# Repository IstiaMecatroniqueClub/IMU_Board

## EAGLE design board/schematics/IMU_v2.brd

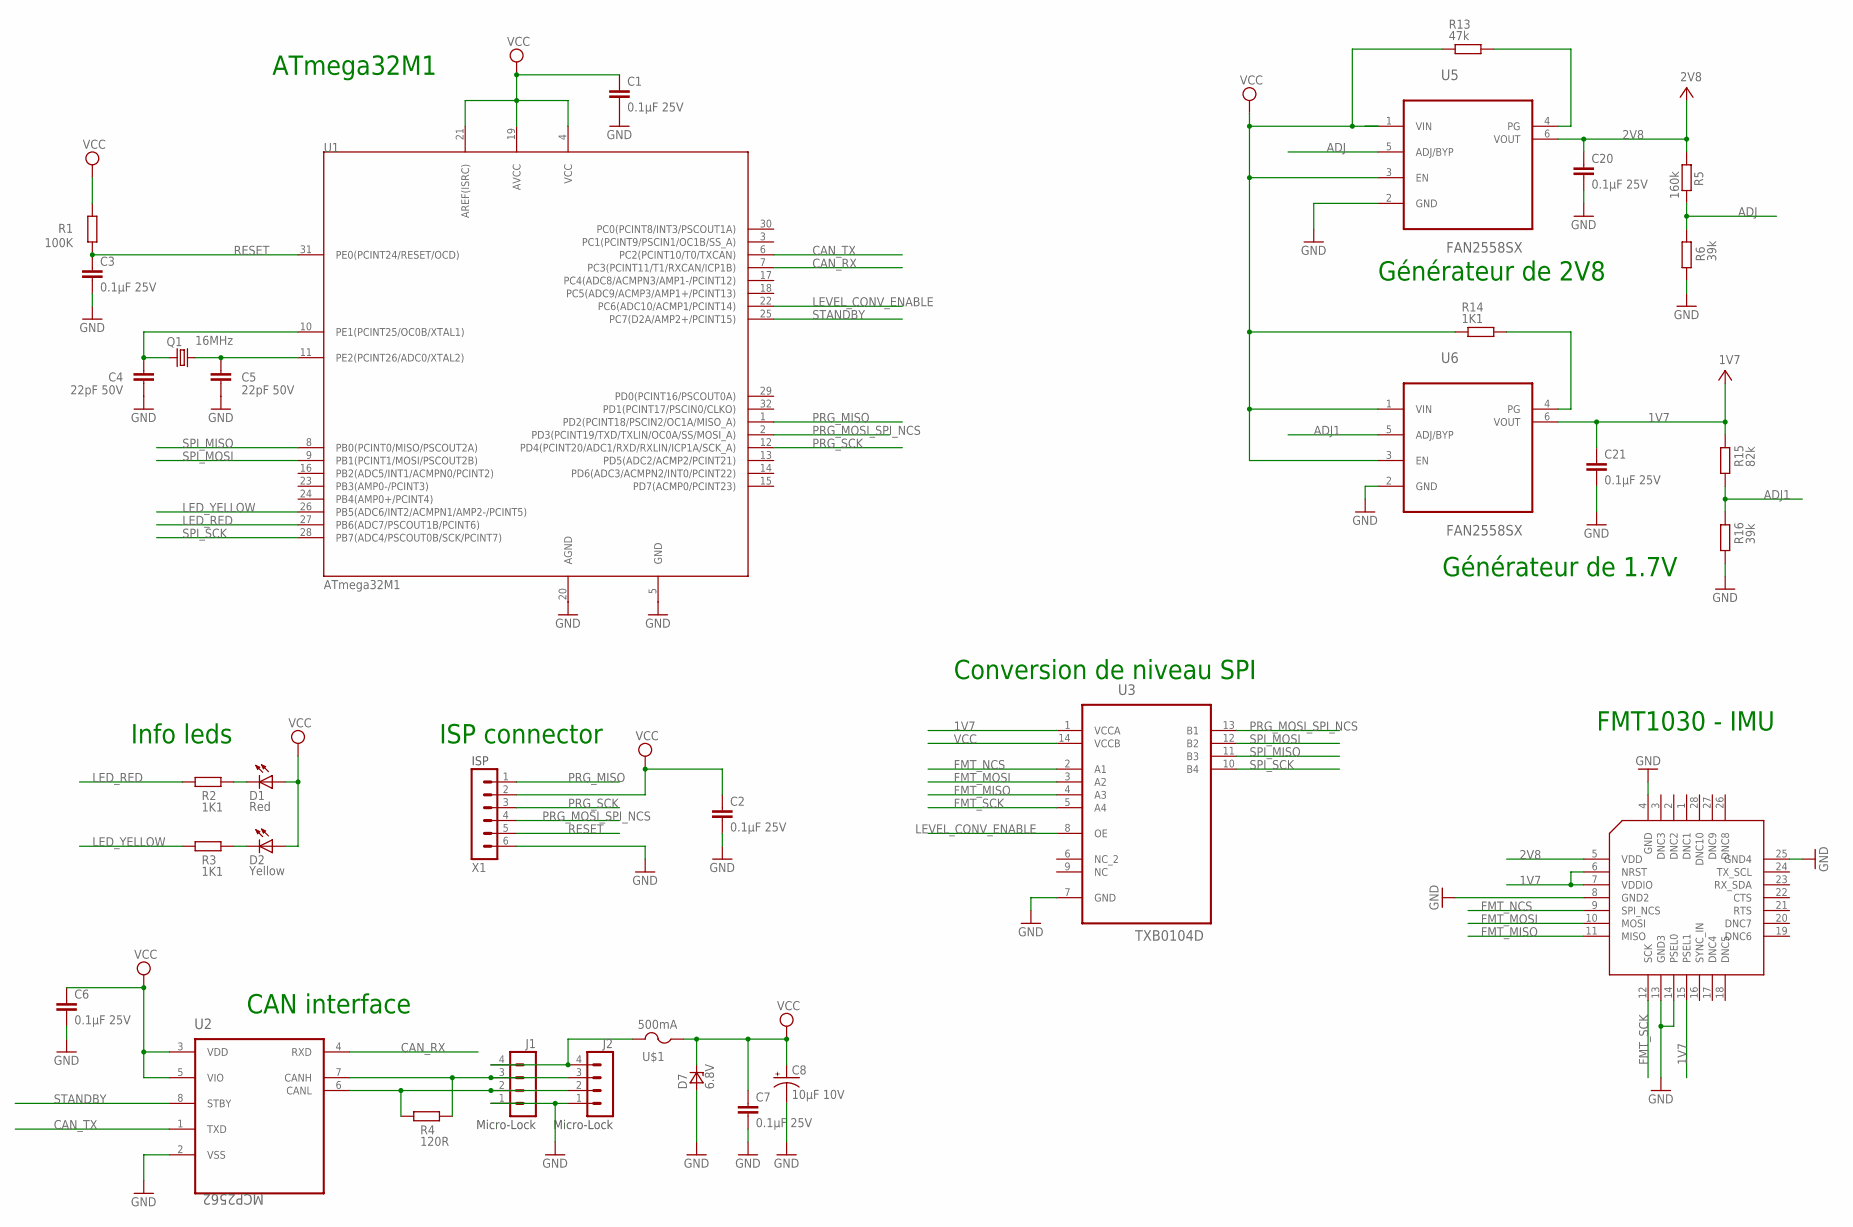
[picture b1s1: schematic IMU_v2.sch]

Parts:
C1, C2, C3, C6, C7, C20, C21: 0.1µF 25V; C2012
C4, C5: 22pF 50V; C2012
C8: 10µF 10V; EIA3216
D1: Red; VLD
D2: Yellow; VLD
D7: 6.8V; DO-214AA
J1, J2: Micro-Lock; 504195-0470
Q1: 16MHz; SMD_KX7
R1: 100K; R2012
R2, R3, R14: 1K1; R2012
R4: 120R; R2012
R5: 160k; R2012
R6, R16: 39k; R2012
R13: 47k; R2012
R15: 82k; R2012
U1: ATmega32M1; TQFP32
U2: MCP2562; SOIC8
U3: TXB0104D; SOIC127P600X175-14N
U5, U6: FAN2558SX; SOT95P270X145-6N
U$1: 500mA; EIARS-481-2
U$2: FMT1030; S28
X1: ISP; MINITEK_127_6WAY_SMD

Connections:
1V7: C21.1, R15.1, U3.1 (VCCA), U6.6 (VOUT), U$2.6 (NRST), U$2.7 (VDDIO), U$2.15 (PSEL1)
2V8: C20.1, R5.1, U5.6 (VOUT), U$2.5 (VDD)
ADJ: R5.2, R6.1, U5.5 (ADJ/BYP)
ADJ1: R15.2, R16.1, U6.5 (ADJ/BYP)
CAN_RX: U1.7 (PC3(PCINT11/T1/RXCAN/ICP1B)), U2.4 (RXD)
CAN_TX: U1.6 (PC2(PCINT10/T0/TXCAN)), U2.1 (TXD)
FMT_MISO: U3.4 (A3), U$2.11 (MISO)
FMT_MOSI: U3.3 (A2), U$2.10 (MOSI)
FMT_NCS: U3.2 (A1), U$2.9 (SPI_NCS)
FMT_SCK: U3.5 (A4), U$2.12 (SCK)
GND: C1.2, C2.2, C3.2, C4.2, C5.2, C6.2, C7.2, C8.C (-), C20.2, C21.2, D7.A, J1.1, J2.1, R6.2, R16.2, U1.5 (GND), U1.20 (AGND), U2.2 (VSS), U3.7 (GND), U5.2 (GND), U6.2 (GND), U$2.4 (GND), U$2.8 (GND2), U$2.13 (GND3), U$2.14 (PSEL0), U$2.25 (GND4), X1.6
LED_RED: R2.2, U1.27 (PB6(ADC7/PSCOUT1B/PCINT6))
LED_YELLOW: R3.2, U1.26 (PB5(ADC6/INT2/ACMPN1/AMP2-/PCINT5))
LEVEL_CONV_ENABLE: U1.22 (PC6(ADC10/ACMP1/PCINT14)), U3.8 (OE)
unnamed: D1.C, R2.1
unnamed: D2.C, R3.1
unnamed: J1.4, J2.4, U$1.2
unnamed: J1.2, J2.2, R4.2, U2.6 (CANL)
unnamed: J1.3, J2.3, R4.1, U2.7 (CANH)
unnamed: C5.1, Q1.3 (2), U1.11 (PE2(PCINT26/ADC0/XTAL2))
unnamed: C4.1, Q1.1, U1.10 (PE1(PCINT25/OC0B/XTAL1))
unnamed: R13.1, U5.4 (PG)
unnamed: R14.2, U6.4 (PG)
PRG_MISO: U1.1 (PD2(PCINT18/PSCIN2/OC1A/MISO_A)), X1.1
PRG_MOSI_SPI_NCS: U1.2 (PD3(PCINT19/TXD/TXLIN/OC0A/SS/MOSI_A)), U3.13 (B1), X1.4
PRG_SCK: U1.12 (PD4(PCINT20/ADC1/RXD/RXLIN/ICP1A/SCK_A)), X1.3
RESET: C3.1, R1.1, U1.31 (PE0(PCINT24/RESET/OCD)), X1.5
SPI_MISO: U1.8 (PB0(PCINT0/MISO/PSCOUT2A)), U3.11 (B3)
SPI_MOSI: U1.9 (PB1(PCINT1/MOSI/PSCOUT2B)), U3.12 (B2)
SPI_SCK: U1.28 (PB7(ADC4/PSCOUT0B/SCK/PCINT7)), U3.10 (B4)
STANDBY: U1.25 (PC7(D2A/AMP2+/PCINT15)), U2.8 (STBY)
VCC: C1.1, C2.1, C6.1, C7.1, C8.A (+), D1.A, D2.A, D7.C, R1.2, R13.2, R14.1, U1.4 (VCC), U1.19 (AVCC), U1.21 (AREF(ISRC)), U2.3 (VDD), U2.5 (VIO), U3.14 (VCCB), U5.1 (VIN), U5.3 (EN), U6.1 (VIN), U6.3 (EN), U$1.1, X1.2

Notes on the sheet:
ISP connector
CAN interface
ATmega32M1
Générateur de 2V8
Générateur de 1.7V
Info leds
Conversion de niveau SPI
FMT1030 - IMU

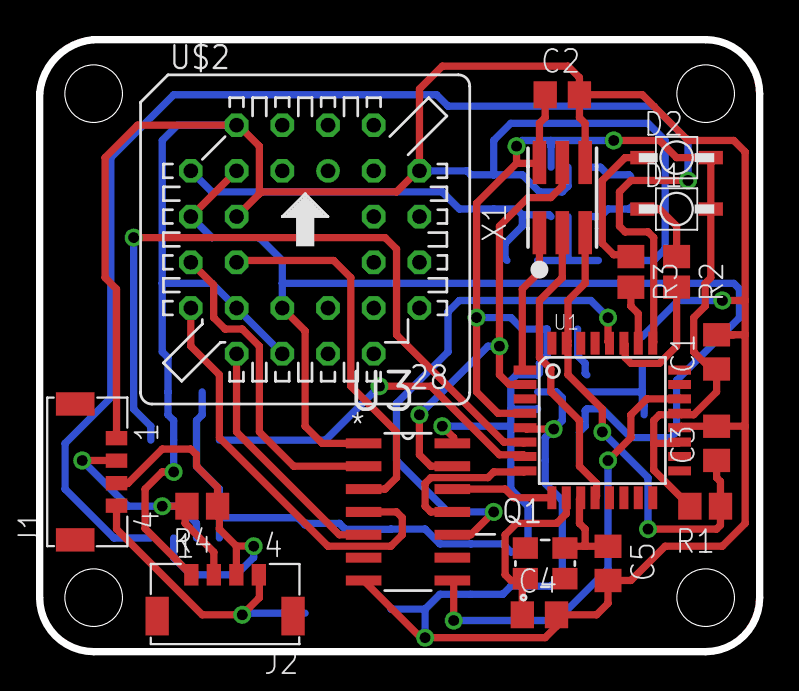
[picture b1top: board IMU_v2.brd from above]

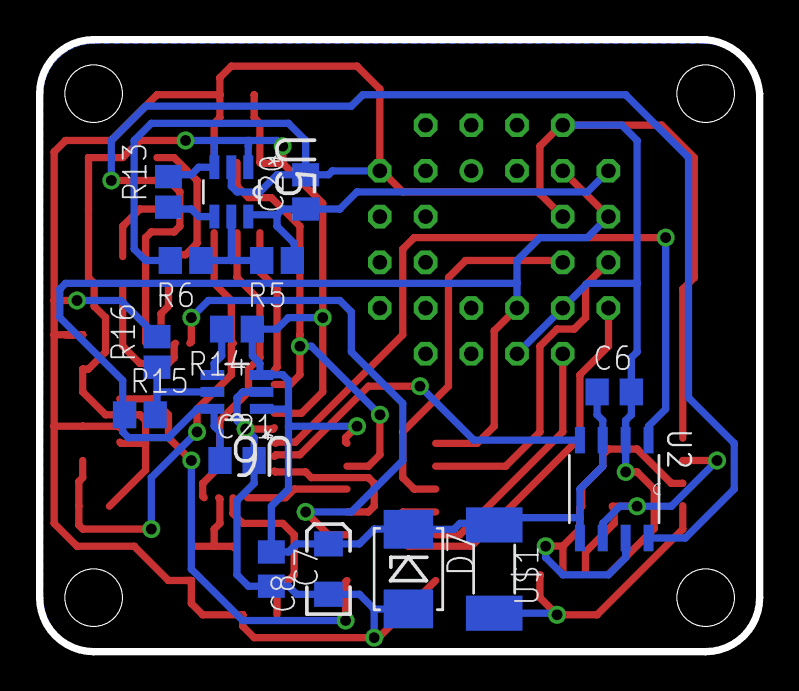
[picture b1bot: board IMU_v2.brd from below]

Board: 2 copper layers, 40.0 x 34.0 mm, 34 parts (16 on the bottom side), 32 nets.

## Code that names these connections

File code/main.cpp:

//! \file main.cpp
//! \brief Main file
//! \author Franck Mercier, Remy Guyonneau
//! \date 2017 05 11
//!
//! Main file for the IMU

#include <util/delay.h>
#include <avr/io.h>
#include <avr/interrupt.h>
#include <string.h> // memcpy


#include "led.h"
#include "spi.h"
#include "fmt1030.h"


// Configuration declaration for the RED LED wiring
#define LED_RED_PORT PORTB //!< The ATMega port where the red LED is wired
#define LED_RED_PIN  6     //!< The ATMega pin where the red LED is wired 
#define LED_RED_POL  0     //!< The polarity of the red LED 

// Configuration declaration for the YELLOW LED wiring
#define LED_YELLOW_PORT PORTB //!< The ATMega port where the red LED is wired
#define LED_YELLOW_PIN  5     //!< The ATMega pin where the red LED is wired 
#define LED_YELLOW_POL  0     //!< The polarity of the red LED 



#define DATA_ID     0X90
#define INPUT_ID    0X77

//! \fn void initCANBus()
//! \brief Intialize the CAN Bus.
//!
//! Function that initializes the CANBus according to the wiring and the needed speed (500kb/s).
//! It also enable the CAN module interruptions
void initCANBus(){
    // Enable of CAN transmit
    DDRC|=0x80; // Configuration of the standby pin as an output
                // (for a transceiver MCP2562 with the stby pin wired to the uC PC7)
    // Enable the MCP2562 (STANDBY to 0)
    PORTC &= 0x7F; // Activation of the MCP2562
                   // (for a transceiver MCP2562 with the stby pin wired to the uC PC7)

    // Initialization of CAN module
    CANGCON  = (1 << SWRES); // Reset CAN module
    CANGCON  = 0x02; // Enable CAN module

    CANBT1 = 0x06; // Speed Config (500kb/s)
    CANBT2 = 0x04;
    CANBT3 = 0x13;

    CANHPMOB = 0x00; // No priority between the CAN MOB

    // Enable CAN interruptions and especially reception interruptions
    CANGIE |= 0xA0;
}

//! \fn void initCANMOB()
//! \brief Intialize the CAN MOB.
//!
//! Intialize the CAN MOB. A MOB can be seen as a "CAN socket".
//! In this case the MOB1 is used to receive remote request
//! and MOB0 is used to send the Ultra sound value
void initCANMOB(){
    CANPAGE = 0x10; // selection of MOB1 (reveice request)

    CANIDT4 = 0x04; // Config as reception remote (rtr = 1)
    CANIDT3 = 0x00;
    CANIDT2 = (uint8_t)( (INPUT_ID & 0x00F)<< 5 ); // using the constant to configure the remote request identifier
    CANIDT1 = (uint8_t)( INPUT_ID >> 3 );

    CANIDM4 = 0x04; // mask over the rtr value
    CANIDM3 = 0xFF; // mask over the identifier (we only want an interruption if the received CAN message is a remote request with the corresponding identifier)
    CANIDM2 = 0xFF;
    CANIDM1 = 0xFF;

    CANCDMOB = 0x80; // Config MOB as reception
    
    CANIE2 = 0x02; // enable the interruptions over the MOB 1

    sei(); // set enable interruption
}


Led redLed(&LED_RED_PORT, LED_RED_PIN, LED_RED_POL); //!< The RED Led
Led yellowLed(&LED_YELLOW_PORT, LED_YELLOW_PIN, LED_YELLOW_POL); //!< The RED Led


void sendCANdata(uint8_t id, uint8_t dlc, uint8_t* data){
CANPAGE  = 0x00; //Selection of MOB 0

CANIDT4 = 0x00; // Config as data (rtr = 0)
CANIDT3 = 0x00;
CANIDT2 = (uint8_t)( (id & 0x00F)<< 5 ); // set the identifier
CANIDT1 = (uint8_t)( id >> 3 );

for(uint8_t i=0; i< dlc; i++){
CANMSG = data[i];
CANPAGE = 0x00 + 1 + i;
}

CANCDMOB = 0x40 + dlc;// send the message using the MOB 0 - DLC = 8

while ( !(CANSTMOB & (1 << TXOK)));
}


//! \fn int main(void)
//! \brief Main function.
//! It makes the led blink when starting, then initialize the CANBus and finally loop forever
int main(void) {

    initCANBus(); // intialization of the CAN Bus
    initCANMOB(); // intialization of the CAN MOB

    DDRC |= 0x40; // Enable SPI level adaptation
    PORTC |= 0x40;

    Fmt1030 imu;
    imu.fmt1030_init();
    MtsspConfiguration notification;
    EulerAngles mesure_angles;

    _delay_ms(200);

    // initialisation de l'IMU
    imu.goToConfig();
    _delay_ms(100);
    imu.setOutputConfiguration(2, XDI_EULERANGLES, 10);
    _delay_ms(100);
    imu.gotoMeasurement();
    _delay_ms(100);

    for(int i=0; i<4; i++){
        redLed.blink(50);
        yellowLed.blink(50);
    }

    //envoi sur bus can des datas
    uint8_t candata[8];

    while(1){
        // lecture du nombre d'octet a lire dans le registre mesure
        notification = imu.read_pipe_status();
        imu.readMesure(notification.measurementMessageSize);

        // lecture du registre mesure
        mesure_angles = imu.getEulerAngles();
 

        candata[0] = 0;
        memcpy(&candata[1], &(mesure_angles.roll), sizeof(float));
        sendCANdata(DATA_ID,5,candata);
        _delay_ms(10);
    
        candata[0] = 1;
        memcpy(&candata[1], &(mesure_angles.pitch), sizeof(float));
        sendCANdata(DATA_ID,5,candata);
        _delay_ms(10);

        candata[0] = 2;
        memcpy(&candata[1], &(mesure_angles.yaw), sizeof(float));
        sendCANdata(DATA_ID,5,candata);

        _delay_ms(100);
    }
}



//! \fn ISR(CAN_INT_vect)
//! \brief CAN interruption.
//! This function is called when an CAN interruption is raised.
//! When it appens, the IMU card blinks...
ISR(CAN_INT_vect){
    cli(); // disable the interruption (no to be disturbed when dealing with one)

    yellowLed.blink(50); // blink the LED
    redLed.blink(50); // blink the LED

    CANPAGE = 0x10; // Selection of MOB 1
    CANSTMOB = 0x00; // Reset the status of the MOB
    CANCDMOB = 0x80; // Config as reception MOB
    CANIE2 = 0x02; // Enable the interuption over MOB 1 (for the next one)

    sei(); // enable the interruptions
}

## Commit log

2017-06-15 Adding source code and schematics
